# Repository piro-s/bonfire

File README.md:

# bonfire
Modernization of the night light bought on Ali in the form of a bonfire from Dark Souls.
The original uses three 5050 RGB LEDs with IR remote control. The range of this control is +- 50 centimeters, you can choose several glow colors. I created a new board to replace the one that was there, without control, just a glow in the form of a fluttering flame (it seems to work). The blue color of the diodes is not used, the red one works constantly, and green, with a PWM, turns out to be flickering yellow, creating the effect of a flame. Everything is controlled by one 48 mega, 6 PWM channels, each controls its own transistor, each has 8 LEDs.

Board size: circle, diameter 98 mm.
v0.1:
1. no remote control (why? It's a fire);
2. instead of 3 LEDs, now 48;
3. work from an external 5V source;
4. consumption about 350mA.

***
## scheme:
### scheme_v0.1:
[pdf](docs/scheme_v0.1.pdf)

***
## pcb:
#### top assambled:

***
## bonfire:
#### assambled:

#### work:

***
## gerber:
Archive for production:
[gerber_v0.1](https://github.com/piro-s/bonfire/raw/master/gerber/bonfire_v0.1.zip)

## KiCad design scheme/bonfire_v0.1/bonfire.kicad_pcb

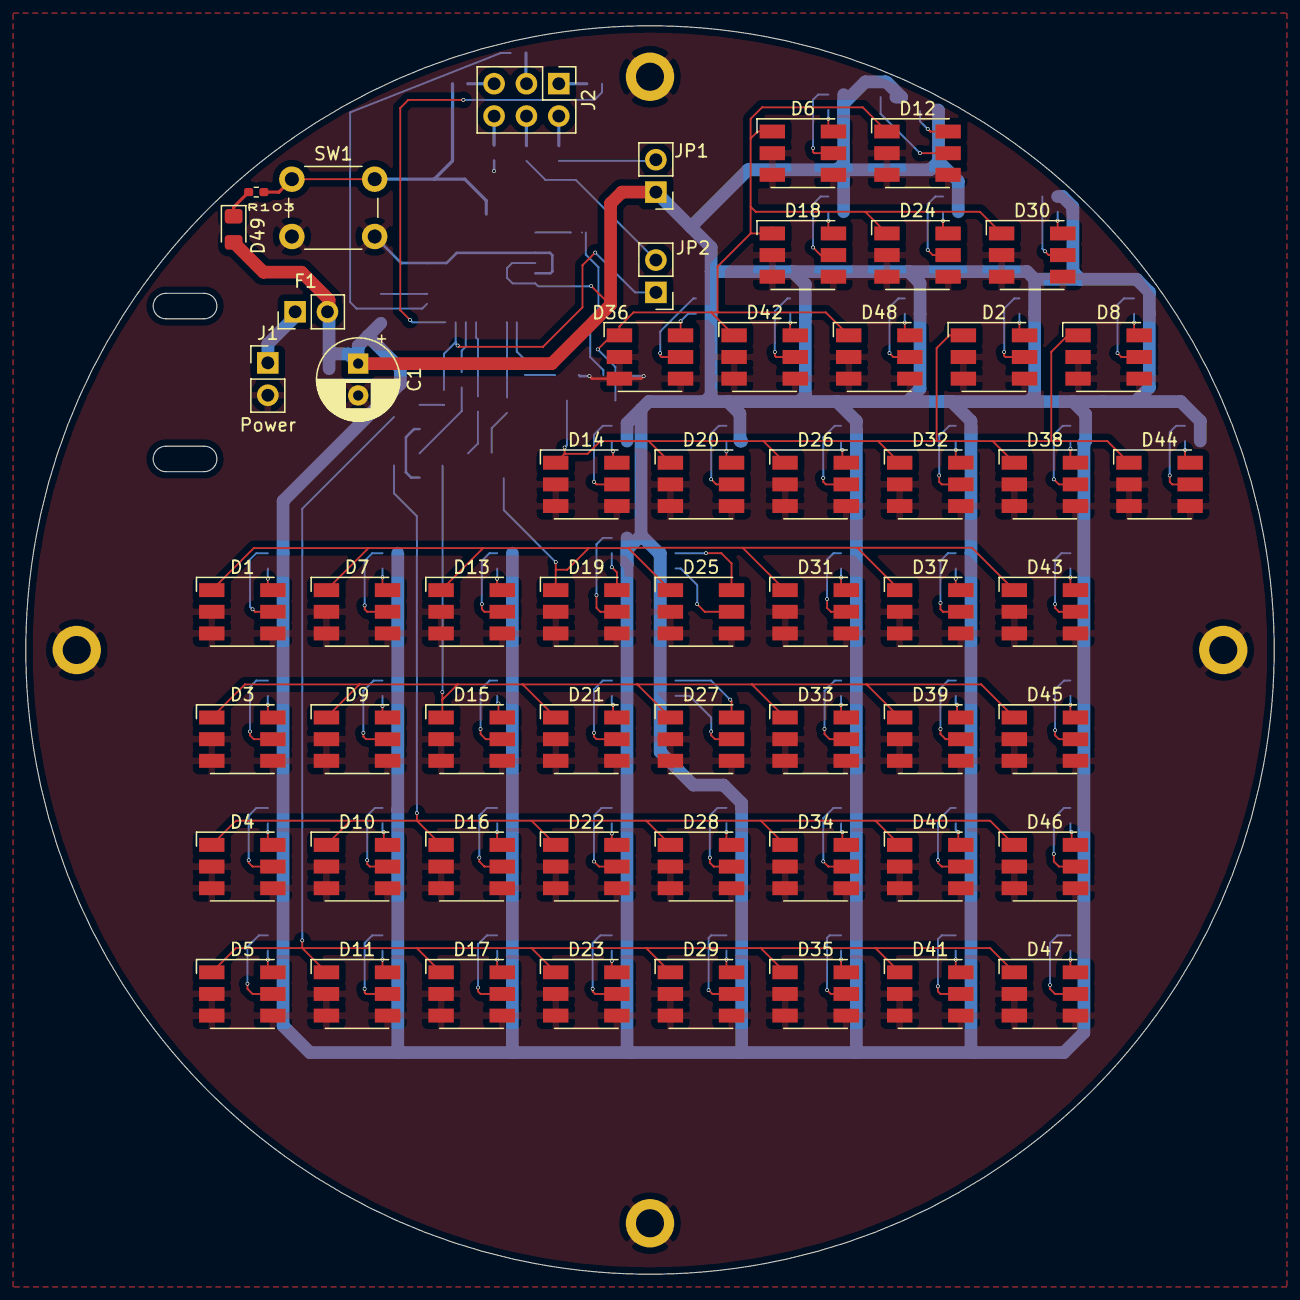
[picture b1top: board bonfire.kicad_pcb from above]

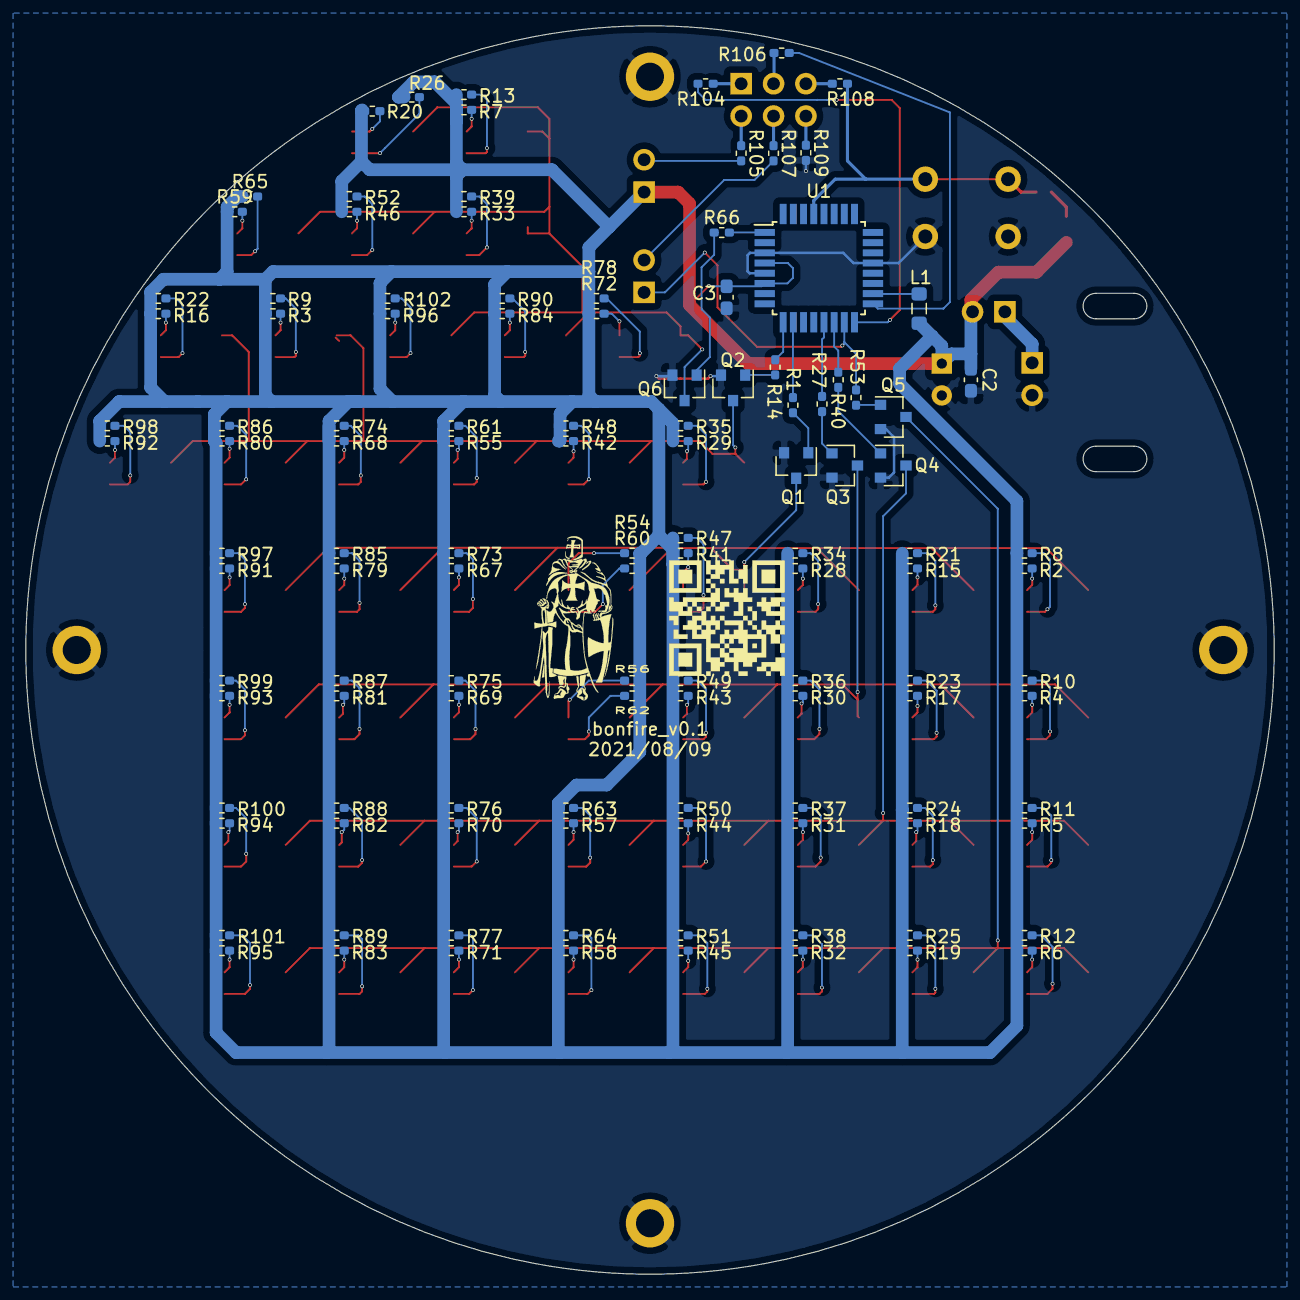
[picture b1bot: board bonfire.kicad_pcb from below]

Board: 2 copper layers, 98.0 x 98.0 mm, 175 parts (118 on the bottom side), 130 nets.

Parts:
C1: 220u; CP_Radial_D6.3mm_P2.50mm
C2, C3: 100n; C_0603_1608Metric_Pad1.08x0.95mm_HandSolder
D1, D2, D3, D4, D5, D6, D7, D8, D9, D10, D11, D12, D13, D14, D15, D16, D17, D18, D19, D20, D21, D22, D23, D24, D25, D26, D27, D28, D29, D30, D31, D32, D33, D34, D35, D36, D37, D38, D39, D40, D41, D42, D43, D44, D45, D46, D47, D48: LED_RGB; LED_RGB_5050-6
D49: LED; LED_0805_2012Metric_Pad1.15x1.40mm_HandSolder
F1: 1A; PinHeader_1x02_P2.54mm_Vertical
J1: Power; PinHeader_1x02_P2.54mm_Vertical
J2: USBASP; PinHeader_2x03_P2.54mm_Vertical
JP1, JP2: Jumper_NO_Small; PinHeader_1x02_P2.54mm_Vertical
L1: 10u; L_0805_2012Metric_Pad1.05x1.20mm_HandSolder
Q1, Q2, Q3, Q4, Q5, Q6: BSS138; SOT-23
R1, R14, R27, R40, R53, R66: 100; R_0402_1005Metric_Pad0.72x0.64mm_HandSolder
R2, R3, R4, R5, R6, R7, R15, R16, R17, R18, R19, R20, R28, R29, R30, R31, R32, R33, R41, R42, R43, R44, R45, R46, R54, R55, R56, R57, R58, R59, R67, R68, R69, R70, R71, R72, R79, R80, R81, R82, R83, R84, R91, R92, R93, R94, R95, R96: 270; R_0402_1005Metric_Pad0.72x0.64mm_HandSolder
R8, R9, R10, R11, R12, R13, R21, R22, R23, R24, R25, R26, R34, R35, R36, R37, R38, R39, R47, R48, R49, R50, R51, R52, R60, R61, R62, R63, R64, R65, R73, R74, R75, R76, R77, R78, R85, R86, R87, R88, R89, R90, R97, R98, R99, R100, R101, R102: 470; R_0402_1005Metric_Pad0.72x0.64mm_HandSolder
R103: 3k3; R_0402_1005Metric_Pad0.72x0.64mm_HandSolder
R104, R106, R107, R108: 10R; R_0402_1005Metric_Pad0.72x0.64mm_HandSolder
R105, R109: 1R8; R_0402_1005Metric_Pad0.72x0.64mm_HandSolder
SW1: Reset; SW_PUSH_6mm
U1: ATmega48-20AU; TQFP-32_7x7mm_P0.8mm

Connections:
+5V: C1.1, C2.1, C3.1, D49.2, F1.2, JP1.1, L1.1, R2.1, R3.1, R4.1, R5.1, R6.1, R7.1, R8.1, R9.1, R10.1, R11.1, R12.1, R13.1, R15.1, R16.1, R17.1, R18.1, R19.1, R20.1, R21.1, R22.1, R23.1, R24.1, R25.1, R26.1, R28.1, R29.1, R30.1, R31.1, R32.1, R33.1, R34.1, R35.1, R36.1, R37.1, R38.1, R39.1, R41.1, R42.1, R43.1, R44.1, R45.1, R46.1, R47.1, R48.1, R49.1, R50.1, R51.1, R52.1, R54.1, R55.1, R56.1, R57.1, R58.1, R59.1, R60.1, R61.1, R62.1, R63.1, R64.1, R65.1, R67.1, R68.1, R69.1, R70.1, R71.1, R72.1, R73.1, R74.1, R75.1, R76.1, R77.1, R78.1, R79.1, R80.1, R81.1, R82.1, R83.1, R84.1, R85.1, R86.1, R87.1, R88.1, R89.1, R90.1, R91.1, R92.1, R93.1, R94.1, R95.1, R96.1, R97.1, R98.1, R99.1, R100.1, R101.1, R102.1, U1.4, U1.6
/MISO: R104.2, U1.16
/RESET: R103.2, R108.2, SW1.1, U1.29
/SCK: R106.2, U1.17
/flame_1: R1.2, U1.10
/flame_2: R14.2, U1.9
/flame_3: R27.2, U1.13
/flame_4: R40.2, U1.14
/flame_5: JP2.1, R53.2, U1.15
/flame_6: R66.2, U1.1
/to_Q1: D1.1, D7.1, D13.1, D19.1, D25.1, D31.1, D37.1, D43.1, Q1.3
/to_Q2: D2.1, D8.1, D14.1, D20.1, D26.1, D32.1, D38.1, D44.1, Q2.3
/to_Q3: D3.1, D9.1, D15.1, D21.1, D27.1, D33.1, D39.1, D45.1, Q3.3
/to_Q4: D4.1, D10.1, D16.1, D22.1, D28.1, D34.1, D40.1, D46.1, Q4.3
/to_Q5: D5.1, D11.1, D17.1, D23.1, D29.1, D35.1, D41.1, D47.1, Q5.3
/to_Q6: D6.1, D12.1, D18.1, D24.1, D30.1, D36.1, D42.1, D48.1, Q6.3
GND: C1.2, C2.2, C3.2, D1.2, D1.3, D1.4, D2.2, D2.3, D2.4, D3.2, D3.3, D3.4, D4.2, D4.3, D4.4, D5.2, D5.3, D5.4, D6.2, D6.3, D6.4, D7.2, D7.3, D7.4, D8.2, D8.3, D8.4, D9.2, D9.3, D9.4, D10.2, D10.3, D10.4, D11.2, D11.3, D11.4, D12.2, D12.3, D12.4, D13.2, D13.3, D13.4, D14.2, D14.3, D14.4, D15.2, D15.3, D15.4, D16.2, D16.3, D16.4, D17.2, D17.3, D17.4, D18.2, D18.3, D18.4, D19.2, D19.3, D19.4, D20.2, D20.3, D20.4, D21.2, D21.3, D21.4, D22.2, D22.3, D22.4, D23.2, D23.3, D23.4, D24.2, D24.3, D24.4, D25.2, D25.3, D25.4, D26.2, D26.3, D26.4, D27.2, D27.3, D27.4, D28.2, D28.3, D28.4, D29.2, D29.3, D29.4, D30.2, D30.3, D30.4, D31.2, D31.3, D31.4, D32.2, D32.3, D32.4, D33.2, D33.3, D33.4, D34.2, D34.3, D34.4, D35.2, D35.3, D35.4, D36.2, D36.3, D36.4, D37.2, D37.3, D37.4, D38.2, D38.3, D38.4, D39.2, D39.3, D39.4, D40.2, D40.3, D40.4, D41.2, D41.3, D41.4, D42.2, D42.3, D42.4, D43.2, D43.3, D43.4, D44.2, D44.3, D44.4, D45.2, D45.3, D45.4, D46.2, D46.3, D46.4, D47.2, D47.3, D47.4, D48.2, D48.3, D48.4, J1.2, Q1.2, Q2.2, Q3.2, Q4.2, Q5.2, Q6.2, R109.2, SW1.2, U1.3, U1.5, U1.21
unnamed: D1.5, R8.2
unnamed: D1.6, R2.2
unnamed: D2.5, R9.2
unnamed: D2.6, R3.2
unnamed: D3.5, R10.2
unnamed: D3.6, R4.2
unnamed: D4.5, R11.2
unnamed: D4.6, R5.2
unnamed: D5.5, R12.2
unnamed: D5.6, R6.2
unnamed: D6.5, R13.2
unnamed: D6.6, R7.2
unnamed: D7.5, R21.2
unnamed: D7.6, R15.2
unnamed: D8.5, R22.2
unnamed: D8.6, R16.2
unnamed: D9.5, R23.2
unnamed: D9.6, R17.2
unnamed: D10.5, R24.2
unnamed: D10.6, R18.2
unnamed: D11.5, R25.2
unnamed: D11.6, R19.2
unnamed: D12.5, R26.2
unnamed: D12.6, R20.2
unnamed: D13.5, R34.2
unnamed: D13.6, R28.2
unnamed: D14.5, R35.2
unnamed: D14.6, R29.2
unnamed: D15.5, R36.2
unnamed: D15.6, R30.2
unnamed: D16.5, R37.2
unnamed: D16.6, R31.2
unnamed: D17.5, R38.2
unnamed: D17.6, R32.2
unnamed: D18.5, R39.2
unnamed: D18.6, R33.2
unnamed: D19.5, R47.2
unnamed: D19.6, R41.2
unnamed: D20.5, R48.2
unnamed: D20.6, R42.2
unnamed: D21.5, R49.2
unnamed: D21.6, R43.2
unnamed: D22.5, R50.2
unnamed: D22.6, R44.2
unnamed: D23.5, R51.2
unnamed: D23.6, R45.2
unnamed: D24.5, R52.2
unnamed: D24.6, R46.2
unnamed: D25.5, R60.2
unnamed: D25.6, R54.2
unnamed: D26.5, R61.2
unnamed: D26.6, R55.2
unnamed: D27.5, R62.2
unnamed: D27.6, R56.2
unnamed: D28.5, R63.2
unnamed: D28.6, R57.2
unnamed: D29.5, R64.2
unnamed: D29.6, R58.2
unnamed: D30.5, R65.2
unnamed: D30.6, R59.2
unnamed: D31.5, R73.2
unnamed: D31.6, R67.2
unnamed: D32.5, R74.2
unnamed: D32.6, R68.2
unnamed: D33.5, R75.2
unnamed: D33.6, R69.2
unnamed: D34.5, R76.2
unnamed: D34.6, R70.2
unnamed: D35.5, R77.2
unnamed: D35.6, R71.2
unnamed: D36.5, R78.2
unnamed: D36.6, R72.2
unnamed: D37.5, R85.2
unnamed: D37.6, R79.2
unnamed: D38.5, R86.2
unnamed: D38.6, R80.2
unnamed: D39.5, R87.2
unnamed: D39.6, R81.2
unnamed: D40.5, R88.2
unnamed: D40.6, R82.2
unnamed: D41.5, R89.2
unnamed: D41.6, R83.2
unnamed: D42.5, R90.2
unnamed: D42.6, R84.2
unnamed: D43.5, R97.2
unnamed: D43.6, R91.2
unnamed: D44.5, R98.2
unnamed: D44.6, R92.2
unnamed: D45.5, R99.2
unnamed: D45.6, R93.2
unnamed: D46.5, R100.2
unnamed: D46.6, R94.2
unnamed: D47.5, R101.2
unnamed: D47.6, R95.2
unnamed: D48.5, R102.2
unnamed: D48.6, R96.2
unnamed: D49.1, R103.1
unnamed: F1.1, J1.1
unnamed: J2.1, R104.1
unnamed: J2.2, R105.1
unnamed: J2.3, R106.1
unnamed: J2.4, R107.1
unnamed: J2.5, R108.1
unnamed: J2.6, R109.1
unnamed: JP1.2, R105.2
unnamed: JP2.2, R107.2
unnamed: L1.2, U1.18
unnamed: Q1.1, R1.1
unnamed: Q2.1, R14.1
unnamed: Q3.1, R27.1
unnamed: Q4.1, R40.1
unnamed: Q5.1, R53.1
unnamed: Q6.1, R66.1

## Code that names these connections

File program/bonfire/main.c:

/*
 * bonfire.c
 *
 * Created: 27.07.2021 9:35:37
 * Author : piro.tex
 */ 


///--- defines
#define F_CPU 1000000UL

#define flame_1 OCR0A
#define flame_2 OCR0B
#define flame_3 OCR1A
#define flame_4 OCR1B
#define flame_5 OCR2A
#define flame_6 OCR2B


///--- includes
#include <avr/io.h>
#include <util/delay.h>


///--- enums
enum flames
{
    // PWM pins
    flame_1_pin     = 6,
    flame_2_pin     = 5,
    flame_3_pin     = 1,
    flame_4_pin     = 2,
    flame_5_pin     = 3,
    flame_6_pin     = 3,
    
    // flames in mass
    flame_1_pos     = 0,
    flame_2_pos     = 1,
    flame_3_pos     = 2,
    flame_4_pos     = 3,
    flame_5_pos     = 4,
    flame_6_pos     = 5,
};


///--- init
void init_PWM(void);
void init_LED(void);


///--- functionts
void flame_pwm(uint8_t flame); // kindle a fire


///--- consts
//const uint8_t flame_max[6] = { 35, 30, 25, 20, 15, 10 };
const uint8_t flame_max[6] = { 50, 40, 30, 20, 10, 8 };


///--- variables
uint8_t flame_val[6] = { 0x00, 0x00, 0x00, 0x00, 0x00, 0x00 }; // pwm value


///-----------------------------------------------------------------------------
int main(void)
{
    init_PWM();
    init_LED();
    
    uint8_t timer = 0;
    
    while(1)
    {       
        if(timer % 25 == 0)
            flame_pwm(flame_6_pos);
        if(timer % 20 == 0)
            flame_pwm(flame_5_pos);
        if(timer % 17 == 0)
            flame_pwm(flame_4_pos);
        if(timer % 9 == 0)
            flame_pwm(flame_3_pos);
        if(timer % 4 == 0)
            flame_pwm(flame_2_pos);
        if(timer % 20 == 0)
            flame_pwm(flame_1_pos);
        
        
        timer++;
        _delay_ms(1);
    } // while (1)
} // int main(void)
///-----------------------------------------------------------------------------


///--- init
void init_PWM(void)
{
    ///--- TIM0 - fast pwm
    TCCR0A = ((1 << COM0A1) | (1 << COM0B1) | (1 << WGM00) | (1 << WGM01));
    TCCR0B |= (1 << CS10);
    TCNT0 = 0x00;
    OCR0A = 0x00;
    OCR0B = 0x00;
    TIMSK0 |= 0x00;
    
    ///--- TIM1 - fast pwm
    TCCR1A = ((1 << COM1A1) | (1 << COM1B1) | (1 << WGM10) | (1 << WGM12));
    TCCR1B |= (1 << CS10);
    TCNT1 = 0x00;
    OCR1A = 0x00;
    OCR1B = 0x00;
    TIMSK1 |= 0x00;
    
    ///--- TIM2 - fast pwm
    TCCR2A = ((1 << COM2A1) | (1 << COM2B1) | (1 << WGM20) | (1 << WGM21));
    TCCR2B |= (1 << CS10);
    TCNT2 = 0x00;
    OCR2A = 0x00;
    OCR2B = 0x00;
    TIMSK2 |= 0x00;
    
    return;
} // void init_PWM(void)

void init_LED(void)
{
    // Ports as out
    DDRD |= ((1 << flame_1_pin) | (1 << flame_2_pin) | (1 << flame_6_pin));
    DDRB |= ((1 << flame_3_pin) | (1 << flame_4_pin) | (1 << flame_5_pin));
    
    // Init ports value
    PORTD &= ~((1 << flame_1_pin) | (1 << flame_2_pin) | (1 << flame_6_pin));
    PORTB &= ~((1 << flame_3_pin) | (1 << flame_4_pin) | (1 << flame_5_pin));
    
    return;
} // void init_LED(void)


///-----------------------------------------------------------------------------
///--- functionts
void flame_pwm(uint8_t flame) // kindle a fire
{
    flame_val[flame]++; // set next pwm value
    if(flame_val[flame] >= flame_max[flame]) // if max pwm
        flame_val[flame] = 0; // set pwm 0
        
    switch(flame)
    {
        case flame_1_pos:
            flame_1 = flame_val[flame]; // set pwm
            break;
        case flame_2_pos:
            flame_2 = flame_val[flame]; // set pwm
            break;
        case flame_3_pos:
            flame_3 = flame_val[flame]; // set pwm
            break;
        case flame_4_pos:
            flame_4 = flame_val[flame]; // set pwm
            break;
        case flame_5_pos:
            flame_5 = flame_val[flame]; // set pwm
            break;
        case flame_6_pos:
            flame_6 = flame_val[flame]; // set pwm
            break;
    } // switch(flame)
    
    return;
} // flame_pwm

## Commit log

2021-10-10 Initial commit
    Modernization of the night light bought on Ali in the form of a bonfire
    from Dark Souls.
